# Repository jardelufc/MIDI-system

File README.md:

# Teremim

O projeto aqui descrito faz parte do Projeto de conclusao da disciplina de Sistema Micro Processados 
Desenvolvedores

-Levir César Ribeiro Lemos 400555

-Mario Victor Rodrigues Sales 408848

O intuito desse projeto é desenvolver um pequeno instrumento musical utilizando um dispositivo ultrassonico e buzzers que mitem um som caracteristico, sendo possivel gravar uma sequencia desses sons e reproduzi-los.
material:
1- stm32f030
2- buzzer
1- hc sr04
3- resistores de 
3- led 
1- protoboard
1 - stlink v2

o Dispositivo é capaz de reproduzir uma sequencia de notas pre definidadas, assim como padroes de cores de led .

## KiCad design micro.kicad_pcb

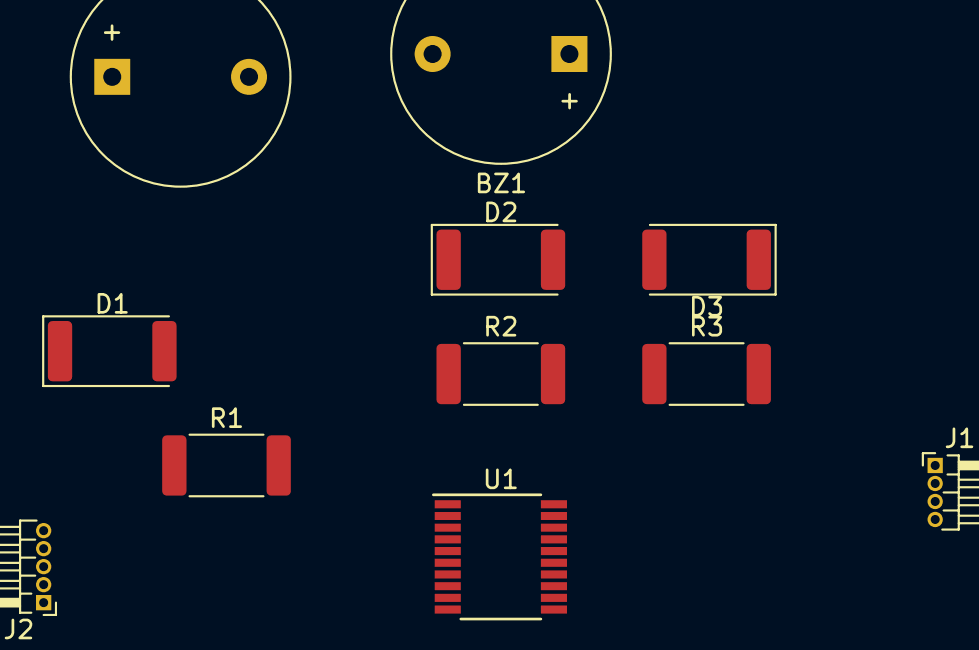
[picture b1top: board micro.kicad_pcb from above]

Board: 2 copper layers, 11 parts (0 on the bottom side), 15 nets, no tracks yet.

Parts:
BZ1, BZ2: Buzzer; Buzzer_12x9.5RM7.6
D1, D2, D3: LED; LED_2512_6332Metric
J1: Ultrassom; PinHeader_1x04_P1.00mm_Horizontal
J2: Conn_01x05_Female; PinHeader_1x05_P1.00mm_Horizontal
R1, R2, R3: R; R_2512_6332Metric
U1: STM32F030F4Px; TSSOP-20_4.4x6.5mm_P0.65mm

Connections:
unnamed: BZ1.1, U1.12
unnamed: BZ1.2, BZ2.2, D1.1, D2.1, D3.1, J1.4, J2.3, U1.15
unnamed: BZ2.1, U1.17
unnamed: D1.2, R1.1
unnamed: D2.2, R2.1
unnamed: D3.2, R3.1
unnamed: J1.1, J2.1
unnamed: J1.2, U1.2
unnamed: J1.3, U1.3
unnamed: J2.2, U1.5, U1.16
unnamed: J2.4, U1.19
unnamed: J2.5, U1.20
unnamed: R1.2, U1.6
unnamed: R2.2, U1.9
unnamed: R3.2, U1.10
